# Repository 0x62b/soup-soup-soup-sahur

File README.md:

# soup-soup-soup-sahur
a programmable nfc badge that go kaboom when plugged into usb

made for hack club [fallout](https://hack.club/fallout) inperson hackathon

REVIEW NOTE: the cost is different to what i thought it was and put on the form; the one in the bom is correct

## BOM
see `bom.csv`

## Screenshots
someone challenged me to make the worst schema i could

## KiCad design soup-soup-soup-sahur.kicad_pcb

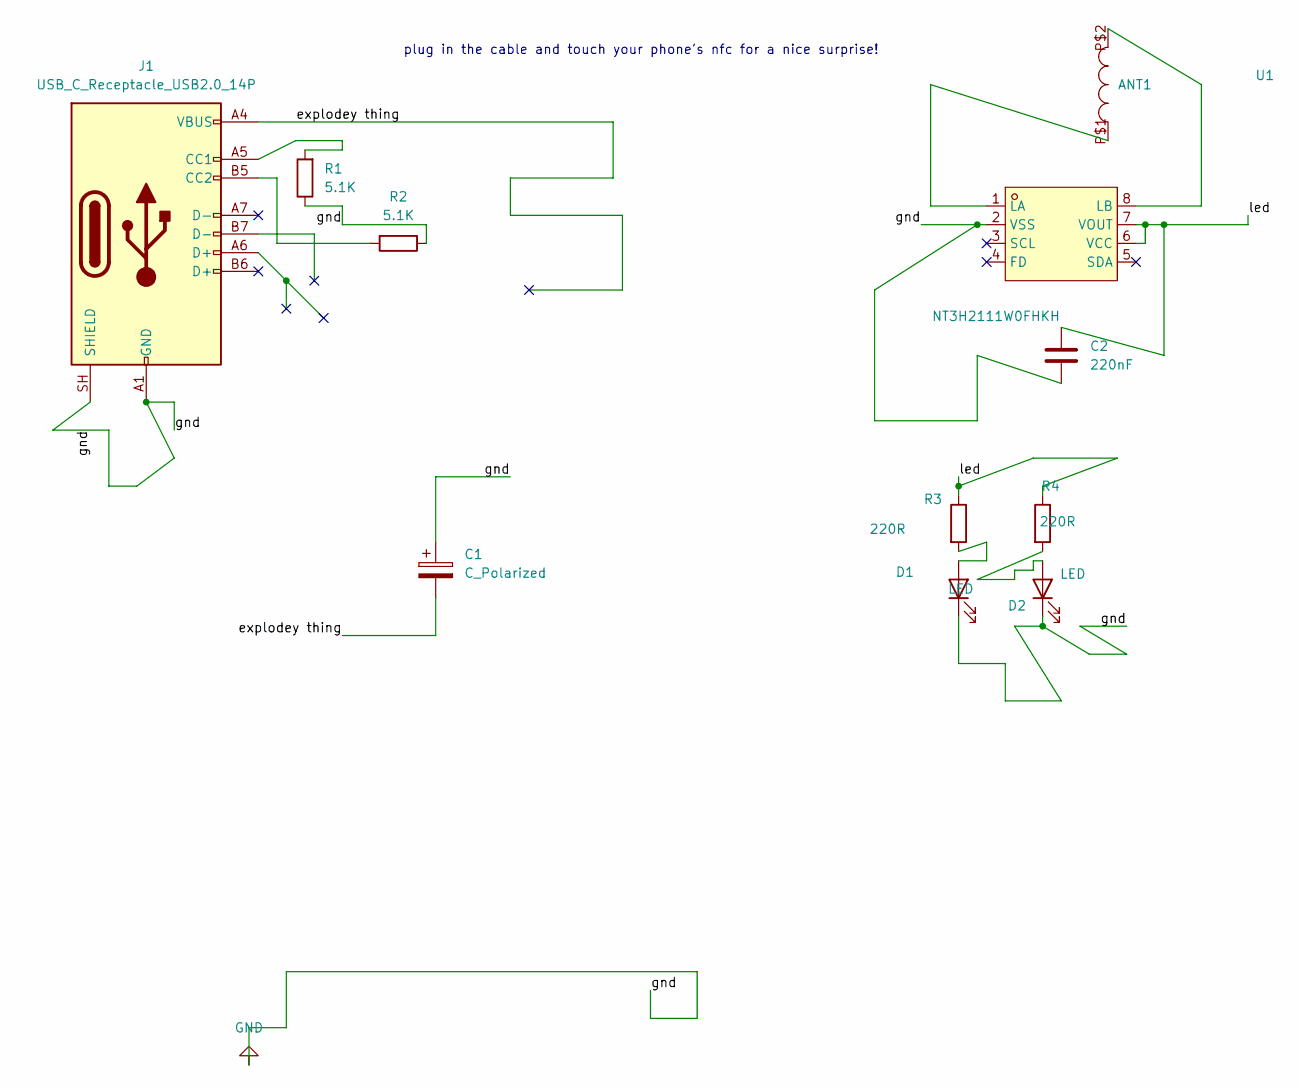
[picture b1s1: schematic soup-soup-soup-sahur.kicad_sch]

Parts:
ANT1: 25X48MM_NFC_ANTENNA
C1: C_Polarized; CP_EIA-7343-20_Kemet-V_HandSolder
C2: 220nF; C_0603_1608Metric_Pad1.08x0.95mm_HandSolder
D1, D2: LED; LED_1206_3216Metric_Pad1.42x1.75mm_HandSolder
J1: USB_C_Receptacle_USB2.0_14P; USB_C_Receptacle_HRO_TYPE-C-31-M-12
R1, R2: 5.1K; R_0603_1608Metric_Pad0.98x0.95mm_HandSolder
R3, R4: 220R; R_0603_1608Metric
U1: NT3H2111W0FHKH; XQFN-8_L1.6-W1.6-P0.50-BL_NT3H2111W0FHKH; MPN NT3H2111W0FHKH; LCSC Part C710403

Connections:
/explodey thing: C1.2, J1.A4 (VBUS), J1.A9 (VBUS), J1.B4 (VBUS), J1.B9 (VBUS)
/led: C2.2, R3.1, R4.1, U1.6 (VCC), U1.7 (VOUT)
GND: C1.1, C2.1, D1.1 (K), D2.1 (K), J1.A1 (GND), J1.A12 (GND), J1.B1 (GND), J1.B12 (GND), J1.SH (SHIELD), R1.1, R2.1, U1.2 (VSS)
unnamed: D1.2 (A), R3.2
unnamed: D2.2 (A), R4.2
unnamed: J1.A5 (CC1), R1.2
unnamed: J1.B5 (CC2), R2.2
unnamed: ANT1.P$1, U1.1 (LA)
unnamed: ANT1.P$2, U1.8 (LB)

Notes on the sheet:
plug in the cable and touch your phone's nfc for a nice surprise!

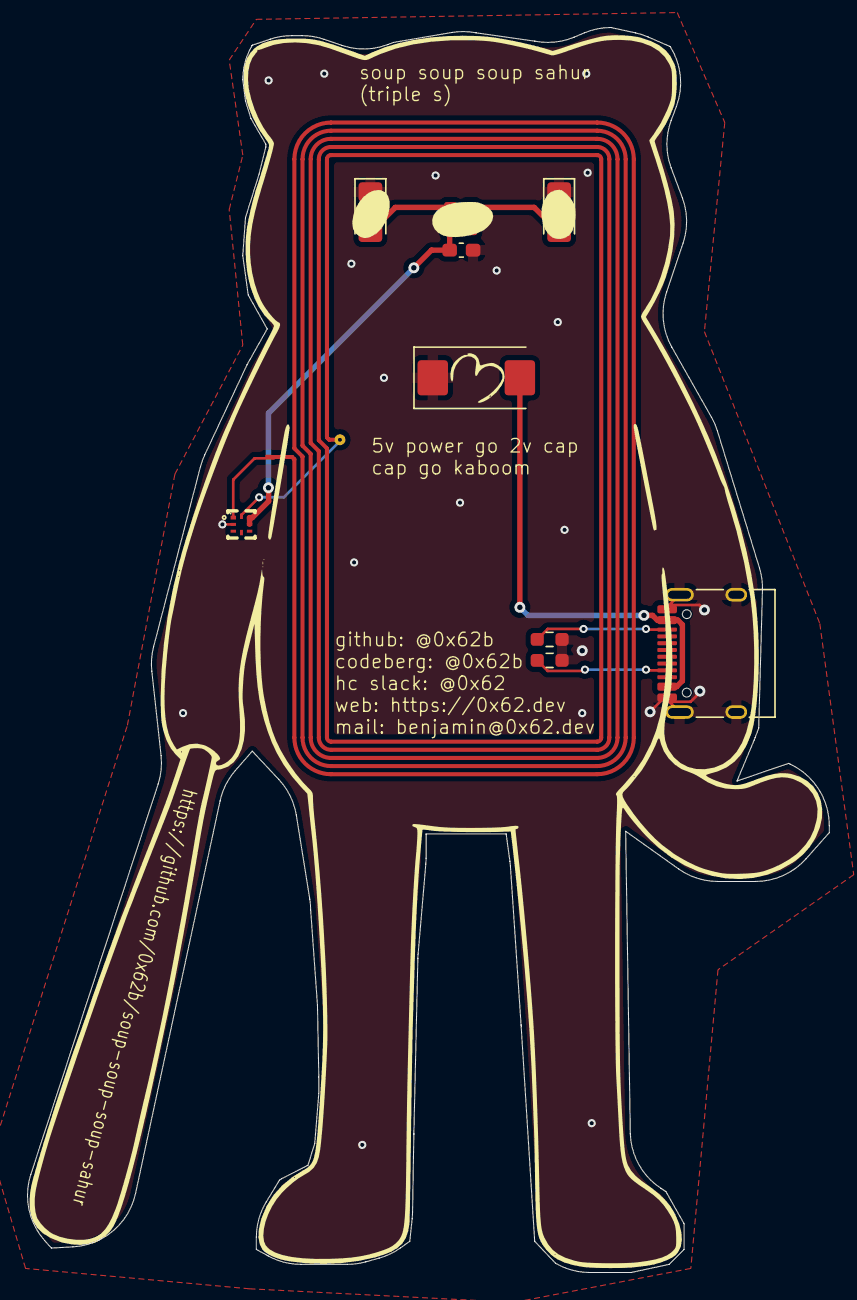
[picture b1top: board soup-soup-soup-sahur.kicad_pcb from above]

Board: 2 copper layers, 59.1 x 91.7 mm, 11 parts (0 on the bottom side), 9 nets.
